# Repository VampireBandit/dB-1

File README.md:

# DB-1

An MP3 player inspired by the Sony  Walkman.Featuring custom UI interactive navigation and minimalism.Bluethooth commectivity and wifi support along with customizable settings. A crush for music lovers

# Images

# Features

-Bluetooh connectivity 

-Wifi integratad

-Long battery life with 2380mah Battery

-Argonomic design

-Rotary encoded volum controll

-4 button navigation

-2.8"   didplay

-Cherry mx switches for fidgety feel

-Custom designed UI

-Unlimited storage(depends on your SD card)

-Programmabe environment

Note: All of the schematic symbols and footprints are not available in KIcad
# BOM

| Name | Purpose | Quantity | Total Cost | Link | Distributor |
| :--- | :--- | :--- | :--- | :--- | :--- |
| **Enclosure** | Casing | 1 | 13 | [Link](https://so) | @Souptik Samanta |
| **PCB** | Circuit board | 5 | 11.3 | [Link](https://jlc) | Aliexpress |
| **Li-Ion Battery** | Powering | 1 | 13.6 | [Link](https://wv) | Aliexpress |
| **47k ohm resistor** | Voltage limit | 1 | 1.47 | [Link](https://wv) | Aliexpress |
| **10k ohm resistor** | Voltage reg | 2 | 1.47 | [Link](https://wv) | Aliexpress |
| **10uf Capacitor** | Voltage reg | 2 | 0.93 | [Link](https://wv) | Aliexpress |
| **HT7533 Regulator** | Power reg | 1 | 1.84 | [Link](https://wv) | Liexpress |
| **Cherry MX Switches** | Navigation | 10 | 9.51 | [Link](https://wv) | Aliexpress |
| **Micro SD card** | Micro SD slot | 1 | 9.57 | [Link](https://wv) | Aliexpress |
| **EC-11 Rotary** | Volume control | 1 | 4.33 | [Link](https://wv) | Aliexpress |
| **2.8 Inch Screen** | Display | 1 | 9.99 | [Link](https://wv) | Aliexpress |
| **TP4056 Charger** | Battery charger | 1 | 3.55 | [Link](https://wv) | Aliexpress |
| **GY-PCM5102** | Audio driver | 1 | 5.35 | [Link](https://wv) | Aliexpress |
| **ESP32-WROOM** | MCU | 1 | 7.72 | [Link](https://wv) | Aliexpress |

Made by Rubaiyat_Islam

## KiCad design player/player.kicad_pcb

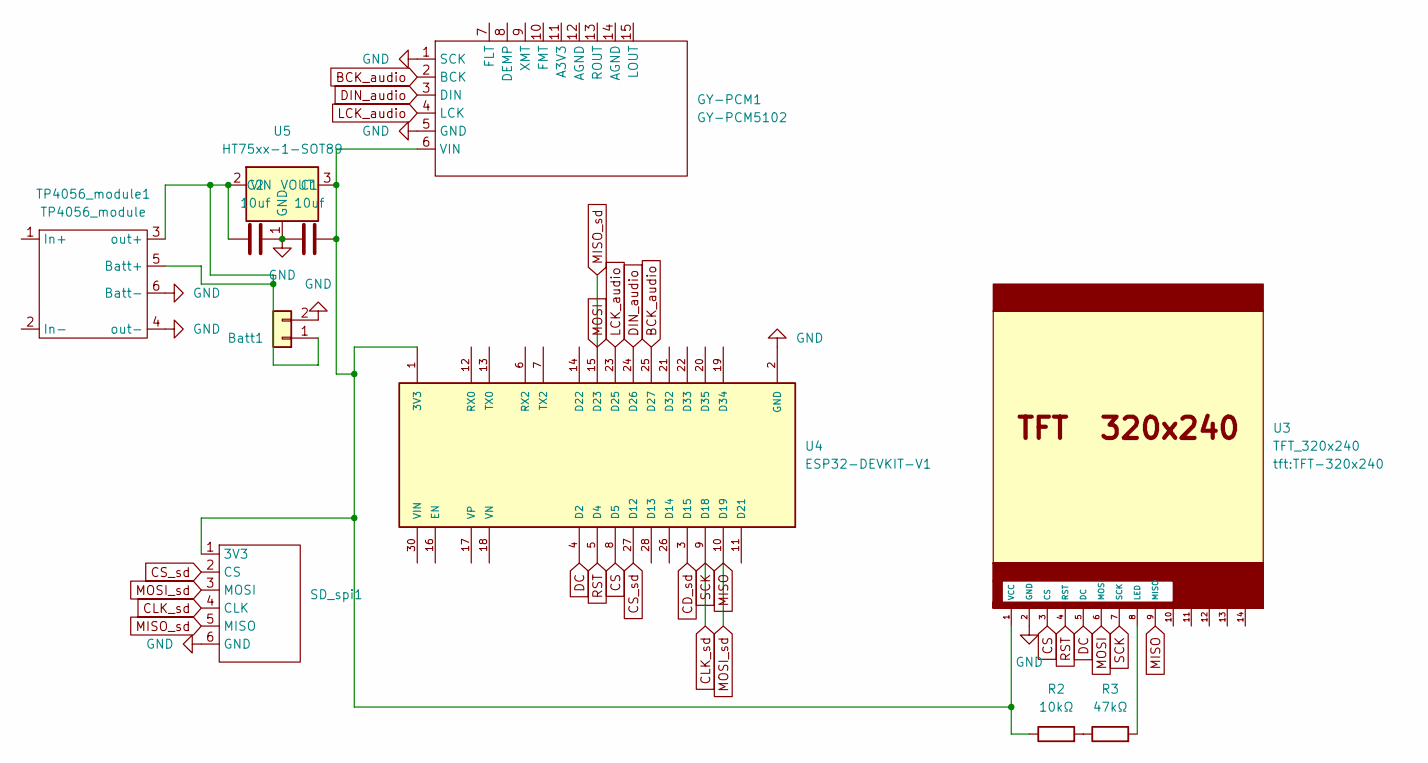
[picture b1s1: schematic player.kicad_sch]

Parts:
Batt1: Conn_01x02; PinHeader_1x02_P2.54mm_Vertical
C1, C2: 10uf; CP_Radial_D5.0mm_P2.00mm
GY-PCM1: GY-PCM5102
R2: 10kΩ; R_Axial_DIN0207_L6.3mm_D2.5mm_P7.62mm_Horizontal
R3: 47kΩ; R_Axial_DIN0207_L6.3mm_D2.5mm_P7.62mm_Horizontal
SD_spi1: SD_spi
TP4056_module1: TP4056_module
U3: TFT_320x240; TFT-320x240
U4: ESP32-DEVKIT-V1; MODULE_ESP32_DEVKIT_V1; PARTREV N/A
U5: HT75xx-1-SOT89; SOT-89-3

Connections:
BCK_audio: GY-PCM1.2 (BCK), U4.25 (D27)
CD_sd: U4.3 (D15)
CLK_sd: SD_spi1.4 (CLK), U3.7 (SCK), U4.9 (D18)
CS: U3.3 (CS), U4.8 (D5)
CS_sd: SD_spi1.2 (CS), U4.27 (D12)
DC: U3.5 (DC), U4.4 (D2)
DIN_audio: GY-PCM1.3 (DIN), U4.24 (D26)
GND: Batt1.2, C1.1, C2.2, GY-PCM1.1 (SCK), GY-PCM1.5 (GND), SD_spi1.6 (GND), TP4056_module1.4 (out-), TP4056_module1.6 (Batt-), U3.2 (GND), U4.2 (GND), U4.29 (GND), U5.1 (GND)
LCK_audio: GY-PCM1.4 (LCK), U4.23 (D25)
MISO: SD_spi1.3 (MOSI), U3.9 (MISO), U4.10 (D19)
MISO_sd: SD_spi1.5 (MISO), U3.6 (MOSI), U4.15 (D23)
unnamed: Batt1.1, C2.1, TP4056_module1.3 (out+), TP4056_module1.5 (Batt+), U5.2 (VIN)
unnamed: C1.2, GY-PCM1.6 (VIN), R2.1, SD_spi1.1 (3V3), U3.1 (VCC), U4.1 (3V3), U5.3 (VOUT)
unnamed: R2.2, R3.1
unnamed: R3.2, U3.8 (LED)
RST: U3.4 (RST), U4.5 (D4)

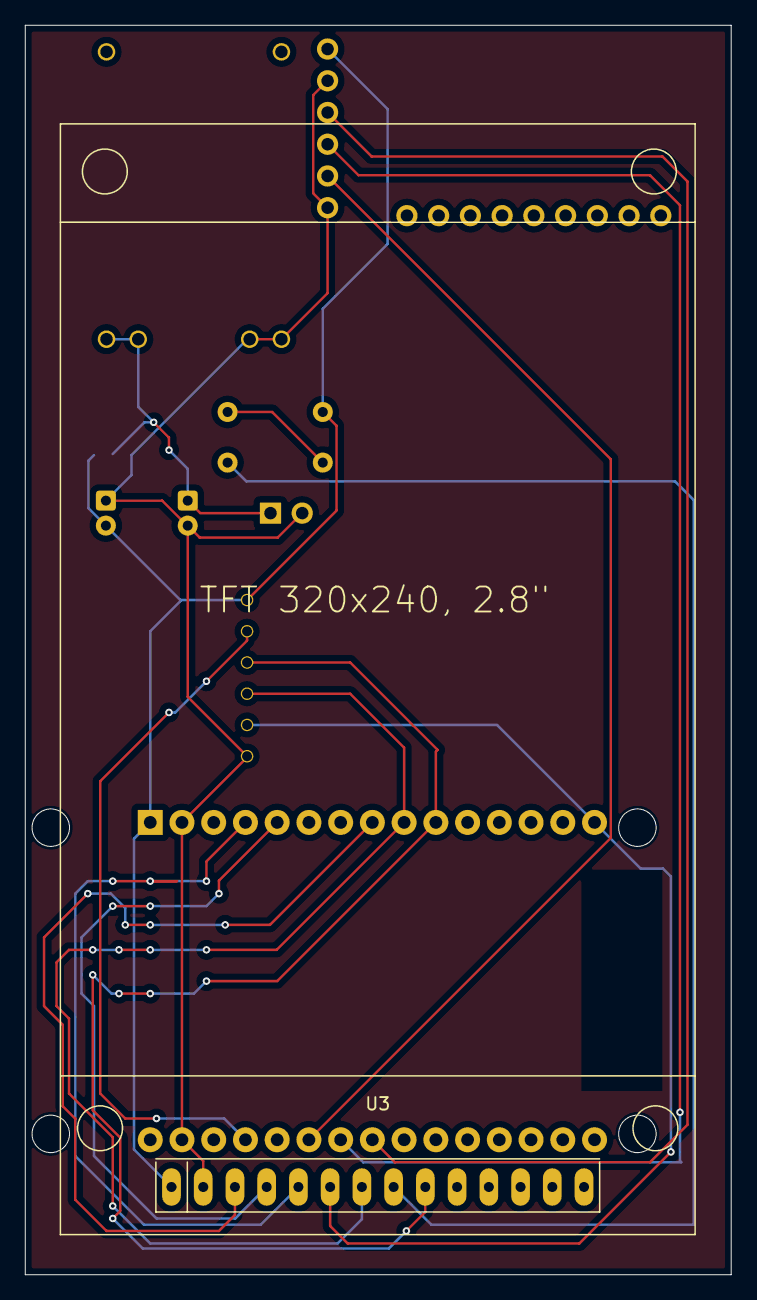
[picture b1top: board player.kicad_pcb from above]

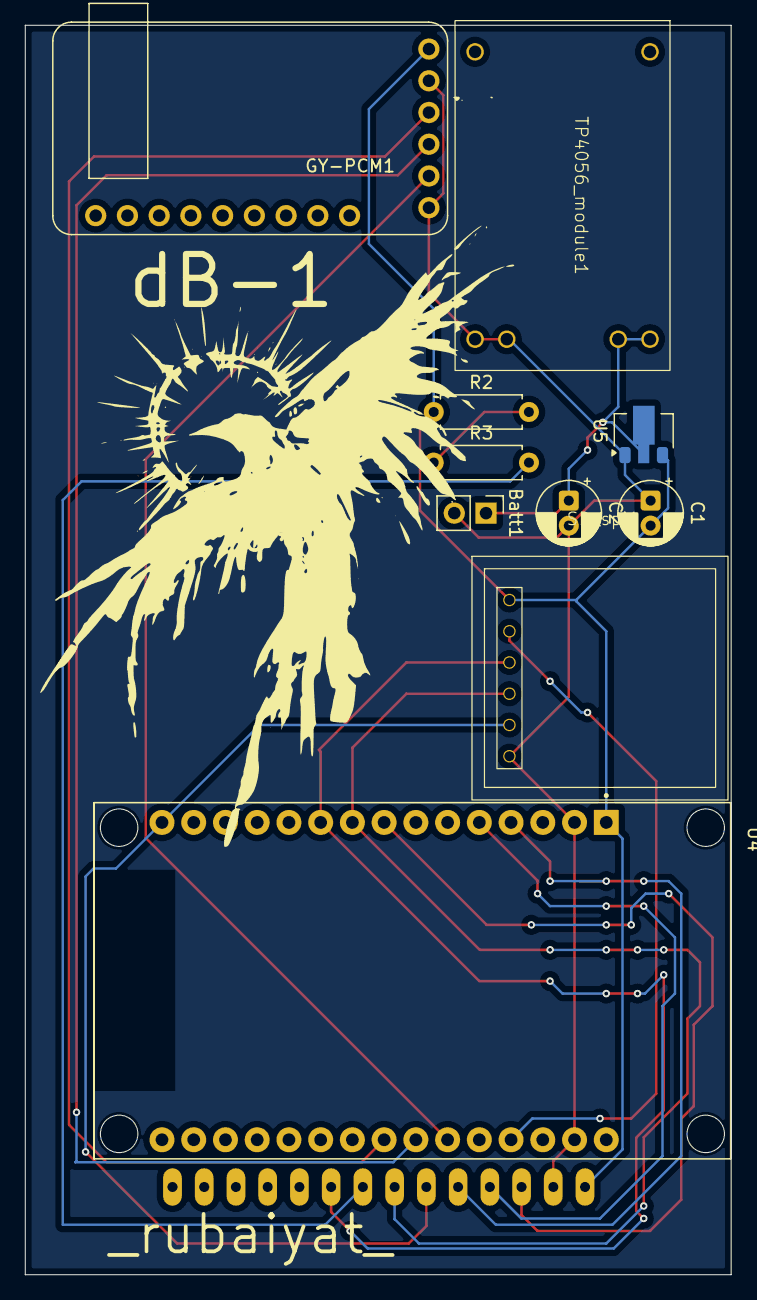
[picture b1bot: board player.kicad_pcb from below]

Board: 2 copper layers, 56.5 x 100.0 mm, 11 parts (10 on the bottom side), 15 nets.

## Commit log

2026-04-10 Made the readme!!
2026-04-16 Update images in README
    Removed Overall image from README and added Over image.
